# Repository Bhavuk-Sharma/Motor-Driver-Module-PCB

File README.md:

# Motor-Driver-Module-PCB
This contains the PCB Board, Schematic and Manufacturing files for Motor Driver Module L298n PCB.
Whole project is made with the help of Autodesk Eagle.

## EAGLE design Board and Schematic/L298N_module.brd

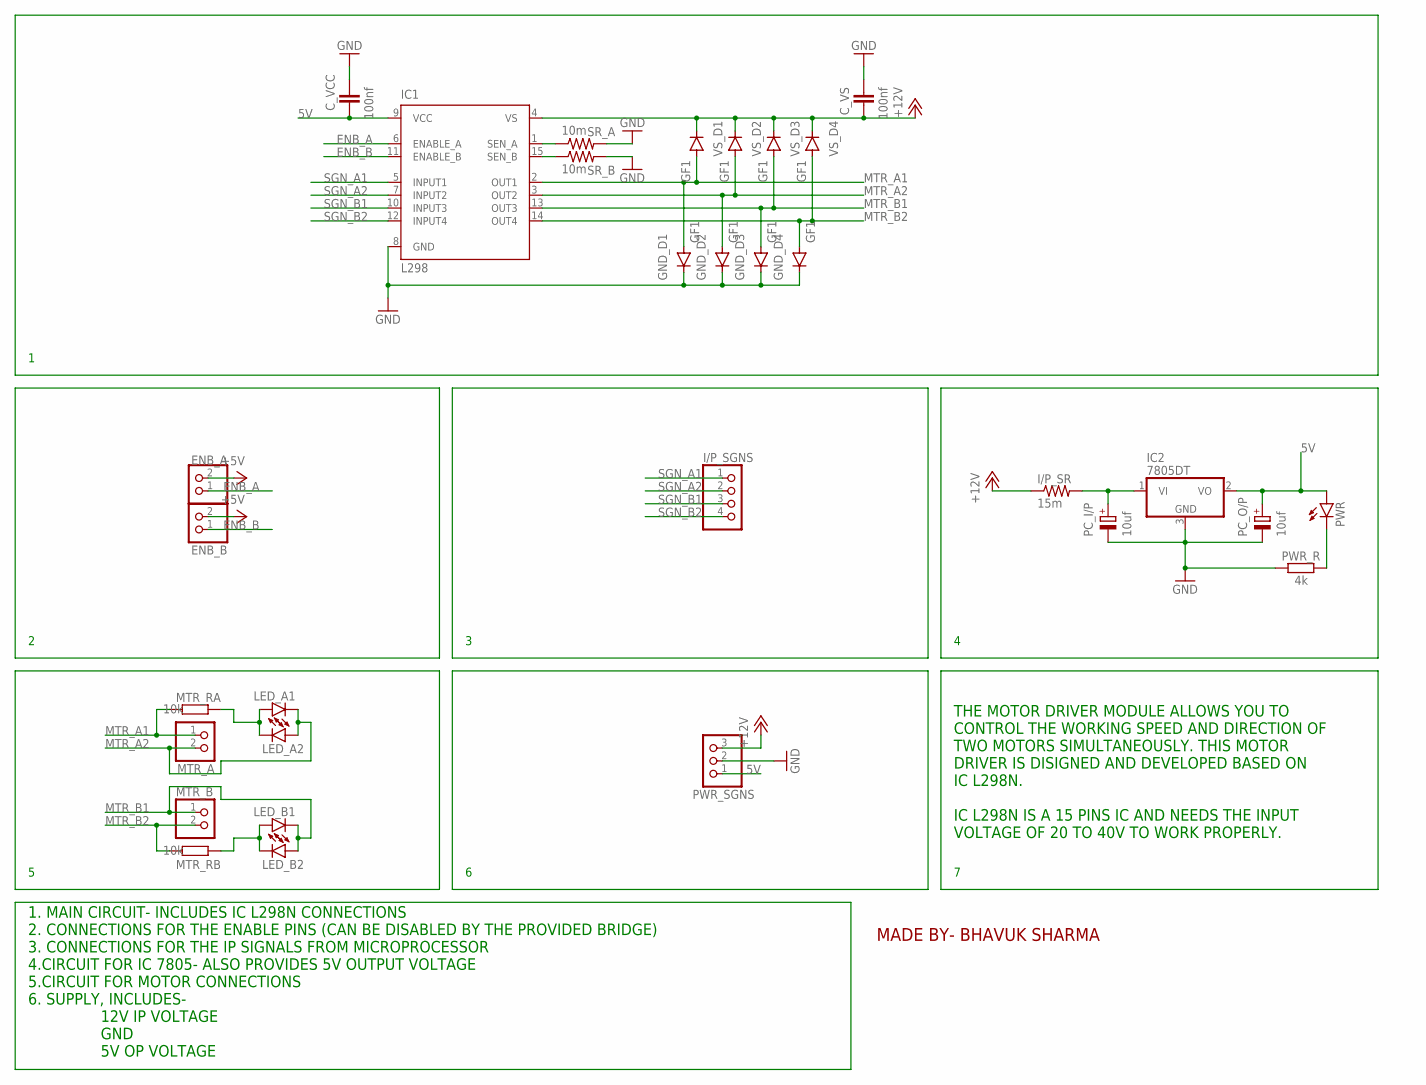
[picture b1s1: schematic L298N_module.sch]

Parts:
C_VCC: 100nf; C025-025X050
C_VS: 100nf; C025-025X050
ENB_A: PINHD-1X2; 1X02
ENB_B: PINHD-1X2; 1X02
GND_D1, GND_D2, GND_D3, GND_D4: GF1; SMA-DO214AC
I/P_SGNS: PINHD-1X4; 1X04
I/P_SR: 15m; 0204/7
IC1: L298; MULTIWATT-15
IC2: 7805DT; TO252
LED_A1, LED_A2: LEDCHIP-LED0805; CHIP-LED0805
LED_B1, LED_B2: LEDCHIP-LED0805; CHIP-LED0805
MTR_A: PINHD-1X2; 1X02
MTR_B: PINHD-1X2; 1X02
MTR_RA: 10k; 0204/7
MTR_RB: 10k; 0204/7
PC_I/P: 10uf; 139CLL-2R
PC_O/P: 10uf; 139CLL-2R
PWR: LED5MM
PWR_R: 4k; 0204/7
PWR_SGNS: PINHD-1X3; 1X03
SR_A: 10m; 0204/7
SR_B: 10m; 0204/7
VS_D1, VS_D2, VS_D3, VS_D4: GF1; SMA-DO214AC

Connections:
5V: C_VCC.1, IC1.9 (VCC), IC2.2 (VO), PC_O/P.+, PWR.A, PWR_SGNS.1
+5V: ENB_A.2, ENB_B.2
+12V: C_VS.1, I/P_SR.1, IC1.4 (VS), PWR_SGNS.3, VS_D1.K (C), VS_D2.K (C), VS_D3.K (C), VS_D4.K (C)
ENB_A: ENB_A.1, IC1.6 (ENABLE_A)
ENB_B: ENB_B.1, IC1.11 (ENABLE_B)
GND: C_VCC.2, C_VS.2, GND_D1.K (C), GND_D2.K (C), GND_D3.K (C), GND_D4.K (C), IC1.8 (GND), IC2.3 (GND), PC_I/P.-, PC_O/P.-, PWR_R.1, PWR_SGNS.2, SR_A.2, SR_B.2
MTR_A1: GND_D1.A, IC1.2 (OUT1), MTR_A.1, MTR_RA.1, VS_D1.A
MTR_A2: GND_D2.A, IC1.3 (OUT2), LED_A1.C, LED_A2.A, MTR_A.2, VS_D2.A
MTR_B1: GND_D3.A, IC1.13 (OUT3), LED_B1.C, LED_B2.A, MTR_B.1, VS_D3.A
MTR_B2: GND_D4.A, IC1.14 (OUT4), MTR_B.2, MTR_RB.1, VS_D4.A
unnamed: LED_A1.A, LED_A2.C, MTR_RA.2
unnamed: PWR.K (C), PWR_R.2
unnamed: IC1.1 (SEN_A), SR_A.1
unnamed: I/P_SR.2, IC2.1 (VI), PC_I/P.+
unnamed: IC1.15 (SEN_B), SR_B.1
unnamed: LED_B1.A, LED_B2.C, MTR_RB.2
SGN_A1: I/P_SGNS.1, IC1.5 (INPUT1)
SGN_A2: I/P_SGNS.2, IC1.7 (INPUT2)
SGN_B1: I/P_SGNS.3, IC1.10 (INPUT3)
SGN_B2: I/P_SGNS.4, IC1.12 (INPUT4)

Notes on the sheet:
1. MAIN CIRCUIT- INCLUDES IC L298N CONNECTIONS 2. CONNECTIONS FOR THE ENABLE PINS (CAN BE DISABLED BY THE PROVIDED BRIDGE) 3. CONNECTIONS FOR THE IP SIGNALS FROM MICROPROCESSOR 4.CIRCUIT FOR IC 7805- ALSO PROVIDES 5V OUTPUT VOLTAGE 5.CIRCUIT FOR MOTOR CONNECTIONS 6. SUPPLY, INCLUDES- 12V IP VOLTAGE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
MADE BY- BHAVUK SHARMA
THE MOTOR DRIVER MODULE ALLOWS YOU TO CONTROL THE WORKING SPEED AND DIRECTION OF TWO MOTORS SIMULTANEOUSLY. THIS MOTOR DRIVER IS DISIGNED AND DEVELOPED BASED ON IC L298N. IC L298N IS A 15 PINS IC AND NEEDS THE INPUT VOLTAGE OF 20 TO 40V TO WORK PROPERLY.

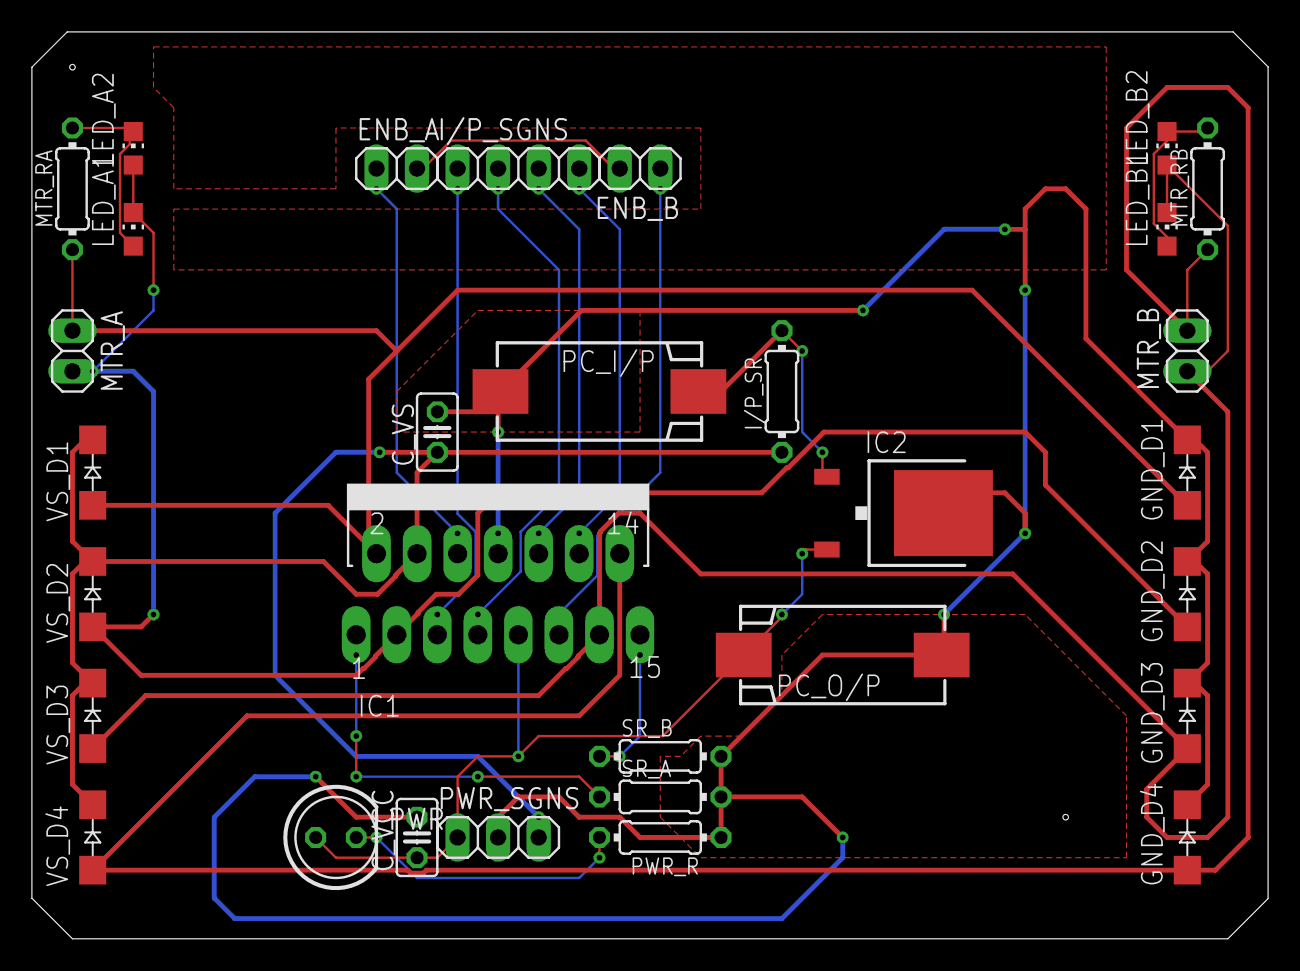
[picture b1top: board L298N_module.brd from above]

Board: 2 copper layers, 77.5 x 56.8 mm, 31 parts (0 on the bottom side), 20 nets.
